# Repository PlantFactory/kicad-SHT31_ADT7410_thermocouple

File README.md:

# kicad-SHT31_ADT7410_thermocouple

SHT31 is used with heating mode for waterproof.
ADT7410 is user as an actual temperature sensor.
Relative humidity is guessed as an applicable equation.

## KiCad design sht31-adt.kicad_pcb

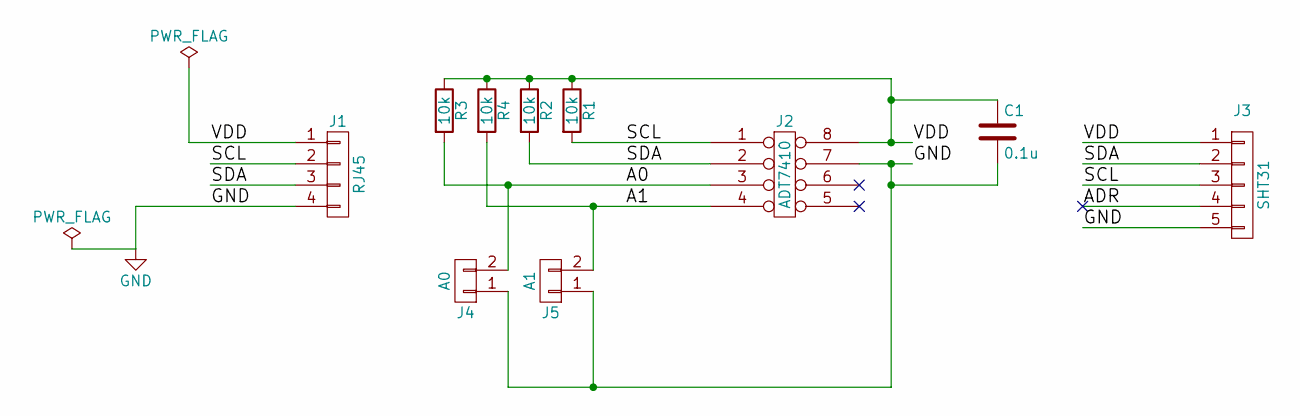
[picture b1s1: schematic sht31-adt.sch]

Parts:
C1: 0.1u; C_0603_HandSoldering
J1: RJ45; Pin_Header_Straight_1x04_Pitch2.54mm
J2: ADT7410; SOIC-8_3.9x4.9mm_Pitch1.27mm
J3: SHT31; Pin_Header_Angled_1x05_Pitch2.54mm
J4: A0; Pin_Header_Straight_1x02_Pitch1.27mm
J5: A1; Pin_Header_Straight_1x02_Pitch1.27mm
R1, R2, R3, R4: 10k; R_0603_HandSoldering

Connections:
/A0: J2.3, J4.2, R3.2
/A1: J2.4, J5.2, R4.2
/ADR: J3.4
/SCL: J1.2, J2.1, J3.3, R1.2
/SDA: J1.3, J2.2, J3.2, R2.2
/VDD: C1.1, J1.1, J2.8, J3.1, R1.1, R2.1, R3.1, R4.1
GND: C1.2, J1.4, J2.7, J3.5, J4.1, J5.1

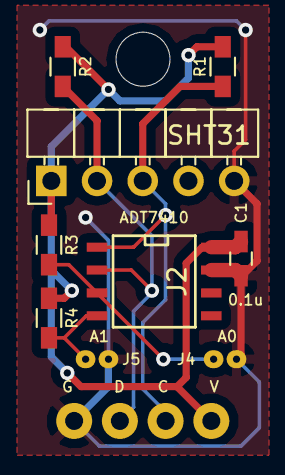
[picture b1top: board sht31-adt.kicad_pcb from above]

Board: 2 copper layers, 10 parts (0 on the bottom side), 6 nets.
